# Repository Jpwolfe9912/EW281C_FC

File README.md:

# EW281C_FC
Flight Controller for EW281C

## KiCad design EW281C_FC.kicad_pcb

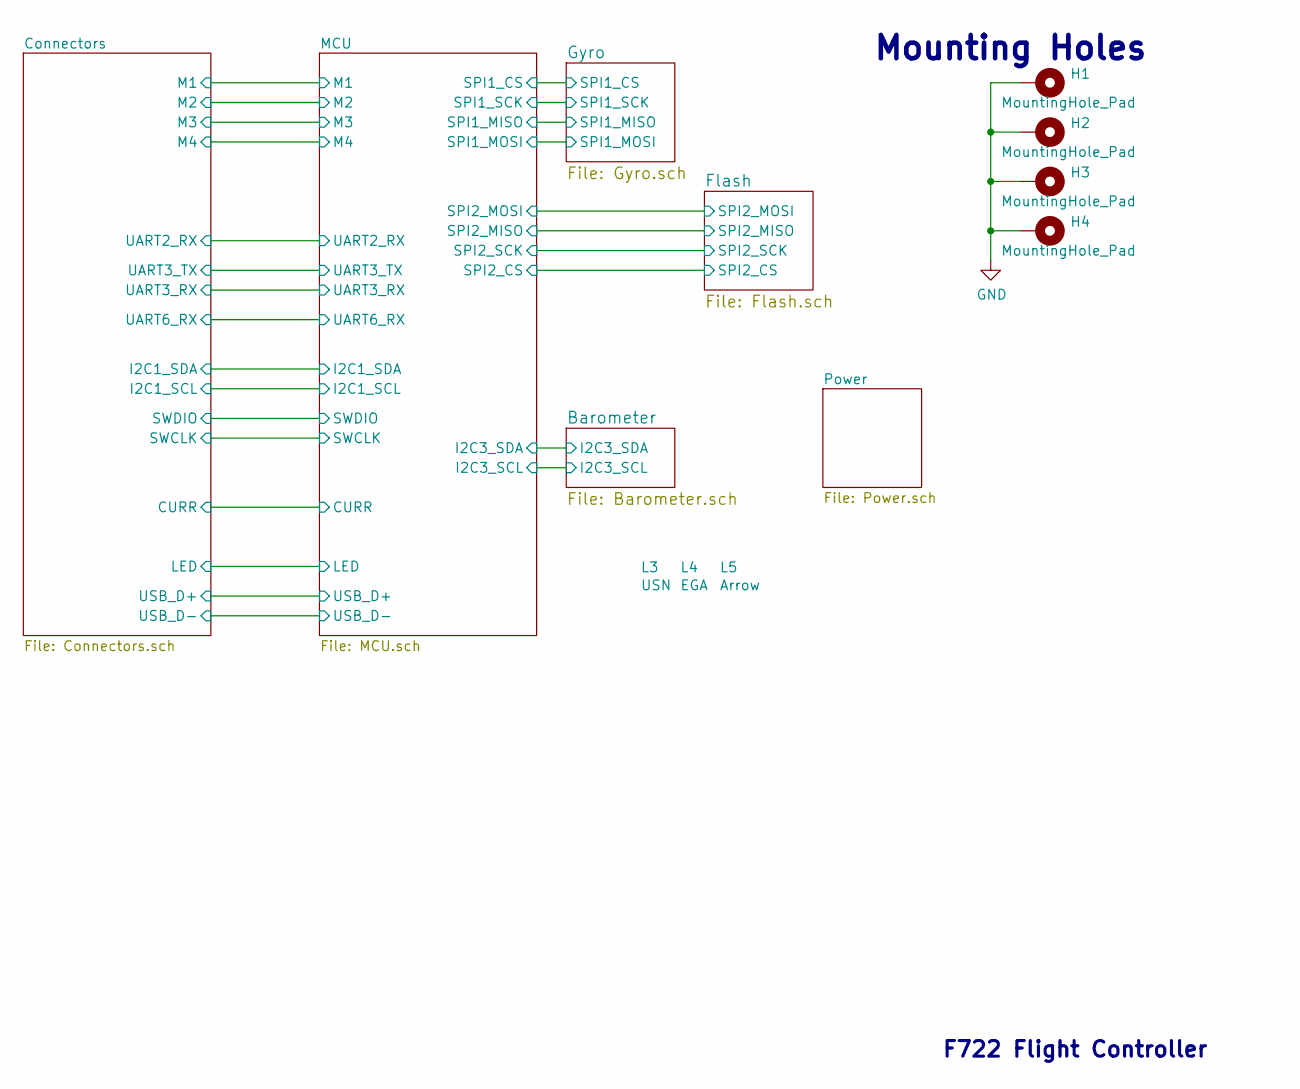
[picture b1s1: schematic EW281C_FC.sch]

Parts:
H1, H2, H3, H4: MountingHole_Pad; MountingHole_3mm_M2_20x20
L3: USN
L4: EGA
L5: Arrow

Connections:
GND: H1.1, H2.1, H3.1, H4.1; also elsewhere on the board

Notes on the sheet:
Mounting Holes
F722 Flight Controller

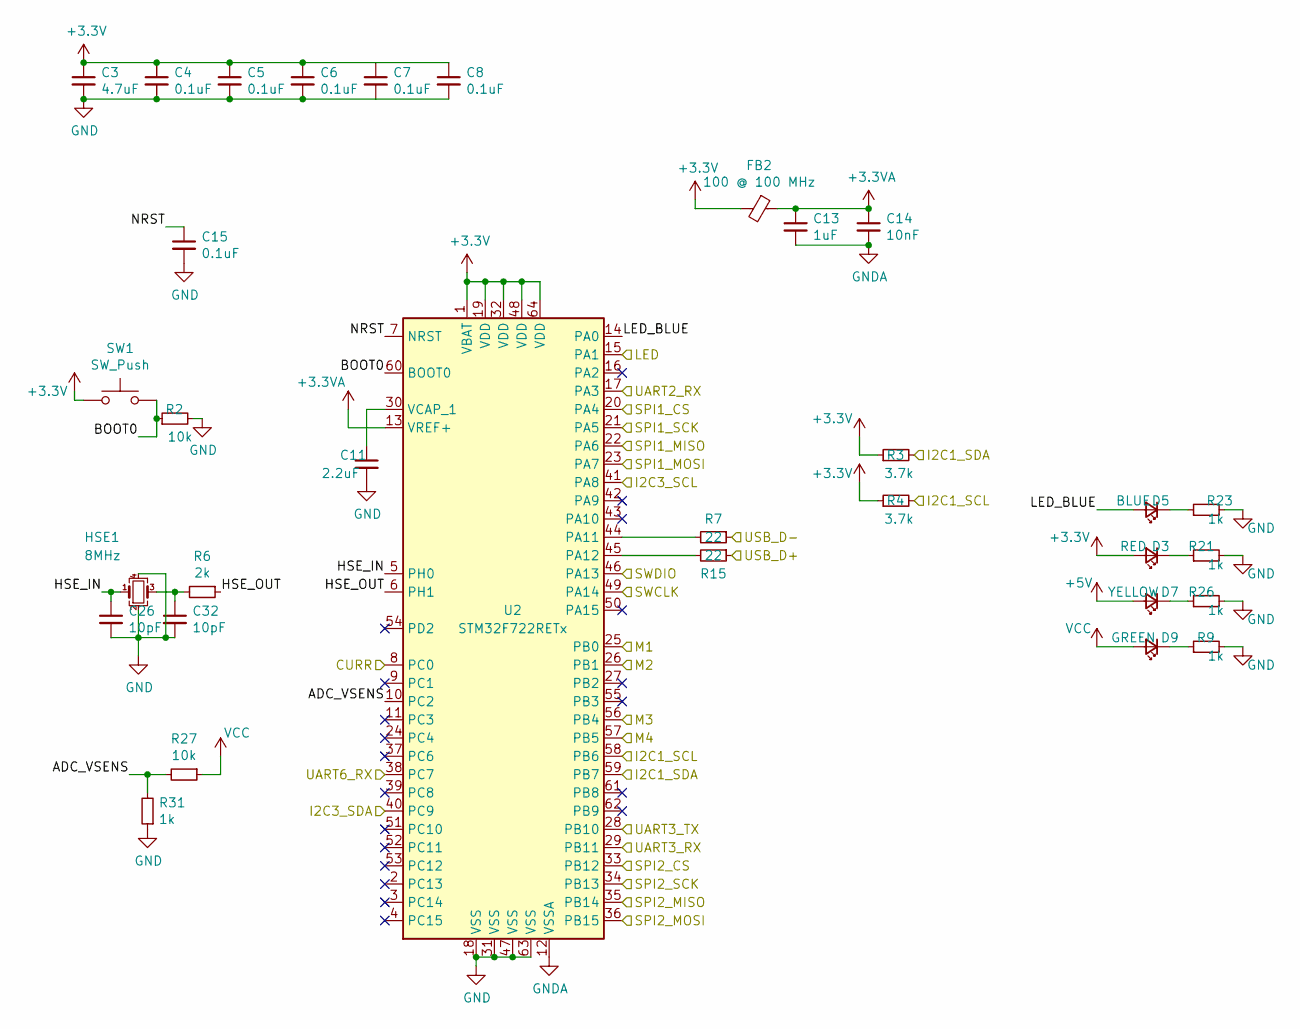
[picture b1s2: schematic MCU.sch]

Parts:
C3: 4.7uF; C_0402_1005Metric
C4, C5, C6, C7, C8, C15: 0.1uF; C_0402_1005Metric
C11: 2.2uF; C_0402_1005Metric
C13: 1uF; C_0402_1005Metric
C14: 10nF; C_0402_1005Metric
C26, C32: 10pF; C_0402_1005Metric
D3: RED; LED_0603_1608Metric
D5: BLUE; LED_0603_1608Metric
D7: YELLOW; LED_0603_1608Metric
D9: GREEN; LED_0603_1608Metric
FB2: 100 @ 100 MHz; L_0603_1608Metric
HSE1: 8MHz; Oscillator_SMD_Abracon_ASE-4Pin_3.2x2.5mm
R2, R27: 10k; R_0402_1005Metric
R3, R4: 3.7k; R_0402_1005Metric
R6: 2k; R_0402_1005Metric
R7, R15: 22; R_0402_1005Metric
R9, R21, R23, R26, R31: 1k; R_0402_1005Metric
SW1: SW_Push; SW_SPST_B3U-1000P
U2: STM32F722RETx; LQFP-64_10x10mm_P0.5mm

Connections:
+3.3VA: C13.1, C14.1, FB2.1, U2.13 (VREF+)
+5V: D7.2 (A); also elsewhere on the board
/Barometer/I2C3_SCL: U2.41 (PA8); also elsewhere on the board
/Barometer/I2C3_SDA: U2.40 (PC9); also elsewhere on the board
/Connectors/CURR: U2.8 (PC0); also elsewhere on the board
/Connectors/I2C1_SCL: R4.2, U2.58 (PB6); also elsewhere on the board
/Connectors/I2C1_SDA: R3.2, U2.59 (PB7); also elsewhere on the board
/Connectors/LED: U2.15 (PA1); also elsewhere on the board
/Connectors/M1: U2.25 (PB0); also elsewhere on the board
/Connectors/M2: U2.26 (PB1); also elsewhere on the board
/Connectors/M3: U2.56 (PB4); also elsewhere on the board
/Connectors/M4: U2.57 (PB5); also elsewhere on the board
/Connectors/SWCLK: U2.49 (PA14); also elsewhere on the board
/Connectors/SWDIO: U2.46 (PA13); also elsewhere on the board
/Connectors/UART2_RX: U2.17 (PA3); also elsewhere on the board
/Connectors/UART3_RX: U2.29 (PB11); also elsewhere on the board
/Connectors/UART3_TX: U2.28 (PB10); also elsewhere on the board
/Connectors/UART6_RX: U2.38 (PC7); also elsewhere on the board
/Connectors/USB_D+: R15.1; also elsewhere on the board
/Connectors/USB_D-: R7.1; also elsewhere on the board
/Flash/SPI2_CS: U2.33 (PB12); also elsewhere on the board
/Flash/SPI2_MISO: U2.35 (PB14); also elsewhere on the board
/Flash/SPI2_MOSI: U2.36 (PB15); also elsewhere on the board
/Flash/SPI2_SCK: U2.34 (PB13); also elsewhere on the board
/Gyro/SPI1_CS: U2.20 (PA4); also elsewhere on the board
/Gyro/SPI1_MISO: U2.22 (PA6); also elsewhere on the board
/Gyro/SPI1_MOSI: U2.23 (PA7); also elsewhere on the board
/Gyro/SPI1_SCK: U2.21 (PA5); also elsewhere on the board
/MCU/ADC_VSENS: R27.2, R31.2, U2.10 (PC2)
/MCU/BOOT0: R2.1, SW1.2, U2.60 (BOOT0)
/MCU/HSE_IN: C26.1, HSE1.1, U2.5 (PH0)
/MCU/HSE_OUT: R6.1, U2.6 (PH1)
/MCU/LED_BLUE: D5.2 (A), U2.14 (PA0)
/MCU/NRST: C15.1, U2.7 (NRST)
GND: C3.2, C4.2, C5.2, C6.2, C7.2, C8.2, C11.2, C15.2, C26.2, C32.2, HSE1.2, HSE1.4, R2.2, R9.2, R21.2, R23.2, R26.2, R31.1, U2.18 (VSS), U2.31 (VSS), U2.47 (VSS), U2.63 (VSS); also elsewhere on the board
GNDA: C13.2, C14.2, U2.12 (VSSA)
unnamed: C11.1, U2.30 (VCAP_1)
unnamed: C32.1, HSE1.3, R6.2
unnamed: D3.1 (K), R21.1
unnamed: D5.1 (K), R23.1
unnamed: D7.1 (K), R26.1
unnamed: D9.1 (K), R9.1
unnamed: R7.2, U2.44 (PA11)
unnamed: R15.2, U2.45 (PA12)
VCC: D9.2 (A), R27.1; also elsewhere on the board

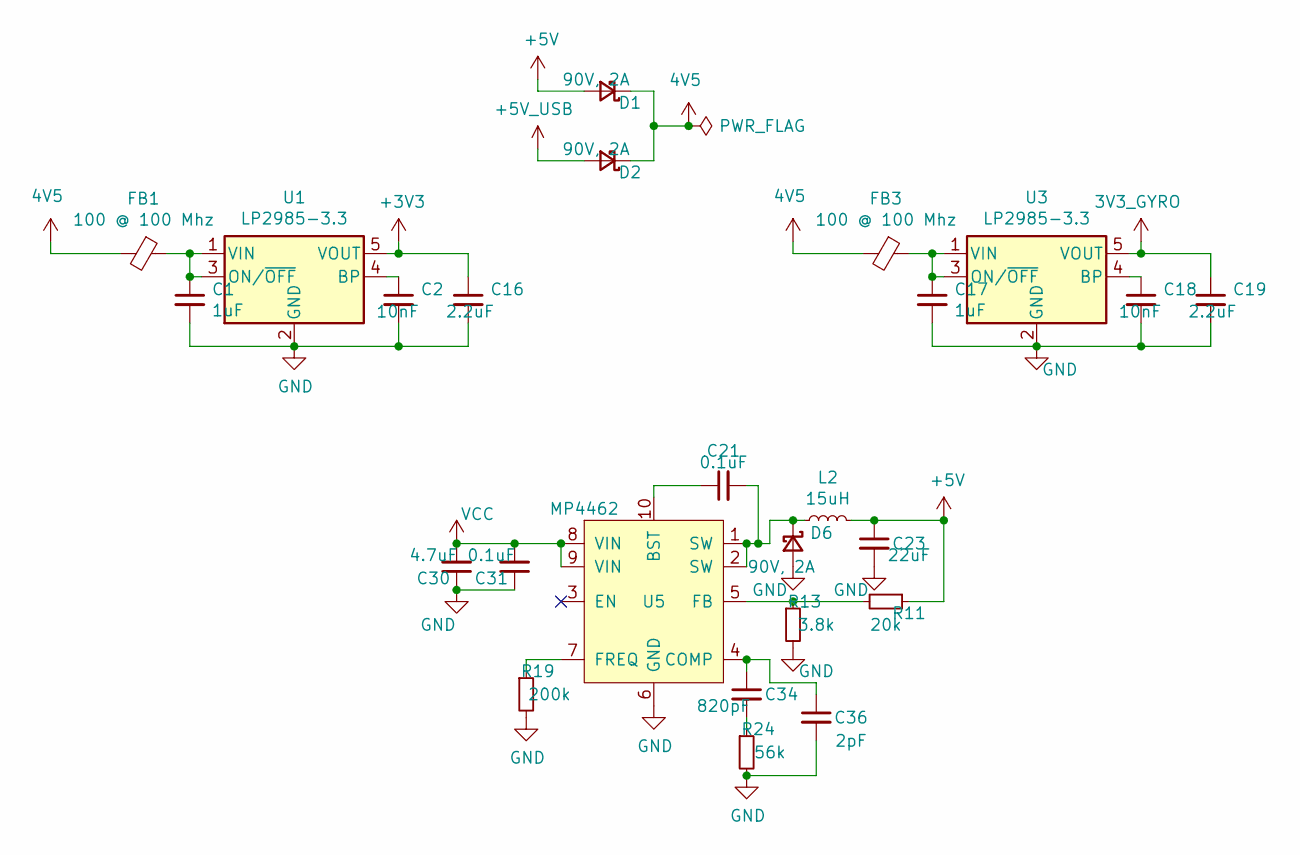
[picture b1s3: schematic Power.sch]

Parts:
C1, C17: 1uF; C_0402_1005Metric
C2, C18: 10nF; C_0402_1005Metric
C16, C19: 2.2uF; C_0402_1005Metric
C21, C31: 0.1uF; C_0402_1005Metric
C23: 22uF; C_0603_1608Metric
C30: 4.7uF; C_0603_1608Metric
C34: 820pF; C_0402_1005Metric
C36: 2pF; C_0402_1005Metric
D1, D2, D6: 90V, 2A; D_SOD-123F
FB1, FB3: 100 @ 100 Mhz; L_0603_1608Metric
L2: 15uH; L_Bourns-SRN3015
R11: 20k; R_0402_1005Metric
R13: 3.8k; R_0402_1005Metric
R19: 200k; R_0402_1005Metric
R24: 56k; R_0402_1005Metric
U1, U3: LP2985-3.3; SOT-23-5
U5: MP4462; DFN-10-1EP_3x3mm_P0.5mm_EP1.7x2.5mm

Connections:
4V5: D1.1 (K), D2.1 (K), FB1.2, FB3.2
+3V3_GYRO: C19.1, U3.5 (VOUT); also elsewhere on the board
+5V: C23.1, D1.2 (A), L2.2, R11.1; also elsewhere on the board
+5V_USB: D2.2 (A); also elsewhere on the board
GND: C1.2, C2.2, C16.2, C17.2, C18.2, C19.2, C23.2, C30.1, C31.1, C36.2, D6.2 (A), R13.2, R19.2, R24.2, U1.2 (GND), U3.2 (GND), U5.6 (GND); also elsewhere on the board
unnamed: C1.1, FB1.1, U1.1 (VIN), U1.3 (ON/~OFF~)
unnamed: C2.1, U1.4 (BP)
unnamed: C17.1, FB3.1, U3.1 (VIN), U3.3 (ON/~OFF~)
unnamed: C18.1, U3.4 (BP)
unnamed: C21.1, U5.10 (BST)
unnamed: C21.2, D6.1 (K), L2.1, U5.1 (SW), U5.2 (SW)
unnamed: C34.1, C36.1, U5.4 (COMP)
unnamed: C34.2, R24.1
unnamed: R11.2, R13.1, U5.5 (FB)
unnamed: R19.1, U5.7 (FREQ)
VCC: C30.2, C31.2, U5.8 (VIN), U5.9 (VIN); also elsewhere on the board

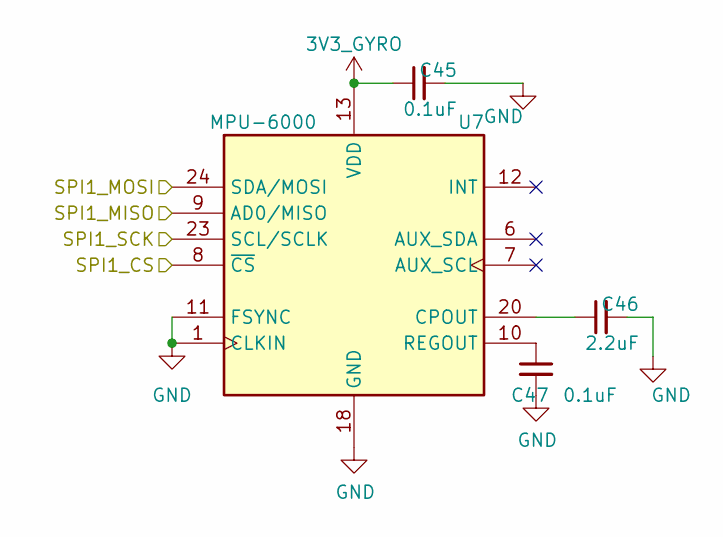
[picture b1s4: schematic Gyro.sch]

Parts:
C45, C47: 0.1uF; C_0402_1005Metric
C46: 2.2uF; C_0402_1005Metric
U7: MPU-6000; InvenSense_QFN-24_4x4mm_P0.5mm

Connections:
+3V3_GYRO: C45.1, U7.13 (VDD); also elsewhere on the board
/Gyro/SPI1_CS: U7.8 (~CS); also elsewhere on the board
/Gyro/SPI1_MISO: U7.9 (AD0/MISO); also elsewhere on the board
/Gyro/SPI1_MOSI: U7.24 (SDA/MOSI); also elsewhere on the board
/Gyro/SPI1_SCK: U7.23 (SCL/SCLK); also elsewhere on the board
GND: C45.2, C46.2, C47.2, U7.1 (CLKIN), U7.11 (FSYNC), U7.18 (GND); also elsewhere on the board
unnamed: C46.1, U7.20 (CPOUT)
unnamed: C47.1, U7.10 (REGOUT)

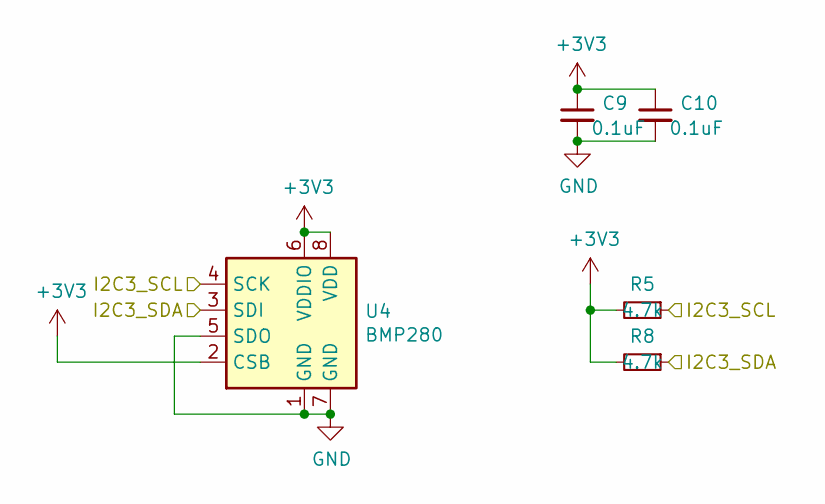
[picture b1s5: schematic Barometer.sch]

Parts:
C9, C10: 0.1uF; C_0402_1005Metric
R5, R8: 4.7k; R_0402_1005Metric
U4: BMP280; Bosch_LGA-8_2x2.5mm_P0.65mm_ClockwisePinNumbering

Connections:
/Barometer/I2C3_SCL: R5.1, U4.4 (SCK); also elsewhere on the board
/Barometer/I2C3_SDA: R8.1, U4.3 (SDI); also elsewhere on the board
GND: C9.2, C10.2, U4.1 (GND), U4.5 (SDO), U4.7 (GND); also elsewhere on the board

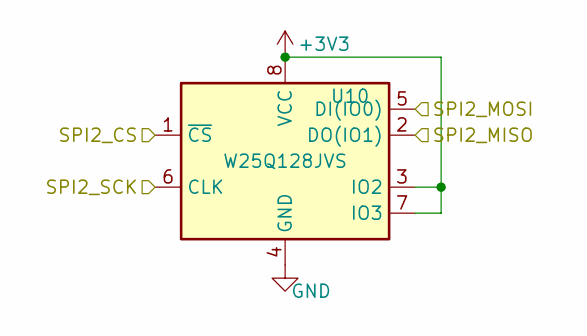
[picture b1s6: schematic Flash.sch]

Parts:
U10: W25Q128JVS; SOIC-8_5.23x5.23mm_P1.27mm

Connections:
/Flash/SPI2_CS: U10.1 (~CS); also elsewhere on the board
/Flash/SPI2_MISO: U10.2 (DO(IO1)); also elsewhere on the board
/Flash/SPI2_MOSI: U10.5 (DI(IO0)); also elsewhere on the board
/Flash/SPI2_SCK: U10.6 (CLK); also elsewhere on the board
GND: U10.4 (GND); also elsewhere on the board

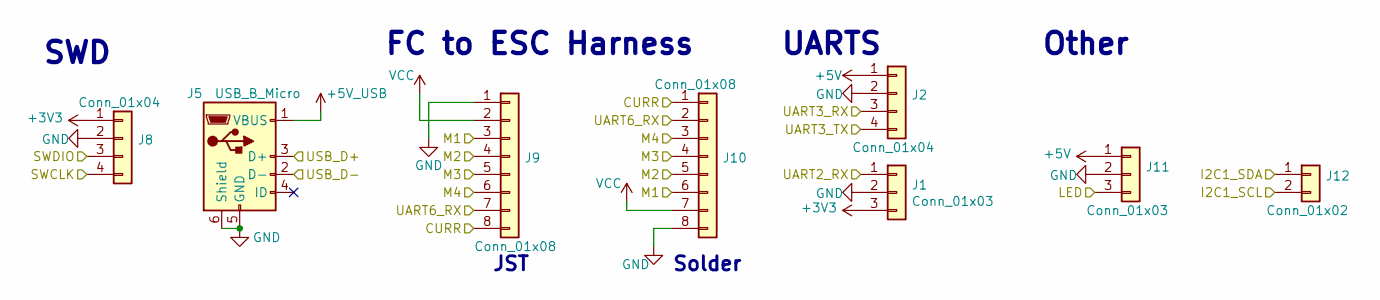
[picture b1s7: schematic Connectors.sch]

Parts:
J1, J11: Conn_01x03; JST_SH_SM03B-SRSS-TB_1x03-1MP_P1.00mm_Horizontal
J2: Conn_01x04; Conn_4Pin
J5: USB_B_Micro; USB_Micro-B_GCT_USB3076-30-A
J8: Conn_01x04; PinHeader_1x04_P2.54mm_Vertical
J9: Conn_01x08; JST_SH_SM08B-SRSS-TB_1x08-1MP_P1.00mm_Horizontal
J10: Conn_01x08; Conn_FC_Solder_8
J12: Conn_01x02; Conn_2Pin

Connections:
+5V: J2.1, J11.1; also elsewhere on the board
+5V_USB: J5.1 (VBUS); also elsewhere on the board
/Connectors/CURR: J9.8, J10.1; also elsewhere on the board
/Connectors/I2C1_SCL: J12.2; also elsewhere on the board
/Connectors/I2C1_SDA: J12.1; also elsewhere on the board
/Connectors/LED: J11.3; also elsewhere on the board
/Connectors/M1: J9.3, J10.6; also elsewhere on the board
/Connectors/M2: J9.4, J10.5; also elsewhere on the board
/Connectors/M3: J9.5, J10.4; also elsewhere on the board
/Connectors/M4: J9.6, J10.3; also elsewhere on the board
/Connectors/SWCLK: J8.4; also elsewhere on the board
/Connectors/SWDIO: J8.3; also elsewhere on the board
/Connectors/UART2_RX: J1.1; also elsewhere on the board
/Connectors/UART3_RX: J2.3; also elsewhere on the board
/Connectors/UART3_TX: J2.4; also elsewhere on the board
/Connectors/UART6_RX: J9.7, J10.2; also elsewhere on the board
/Connectors/USB_D+: J5.3 (D+); also elsewhere on the board
/Connectors/USB_D-: J5.2 (D-); also elsewhere on the board
GND: J1.2, J2.2, J5.5 (GND), J5.6 (Shield), J8.2, J9.1, J10.8, J11.2; also elsewhere on the board
VCC: J9.2, J10.7; also elsewhere on the board

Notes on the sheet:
FC to ESC Harness
UARTS
SWD
Other
JST
Solder

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
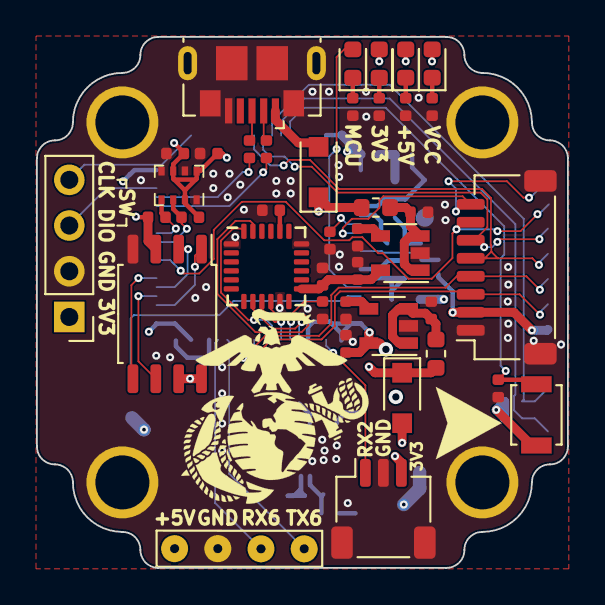
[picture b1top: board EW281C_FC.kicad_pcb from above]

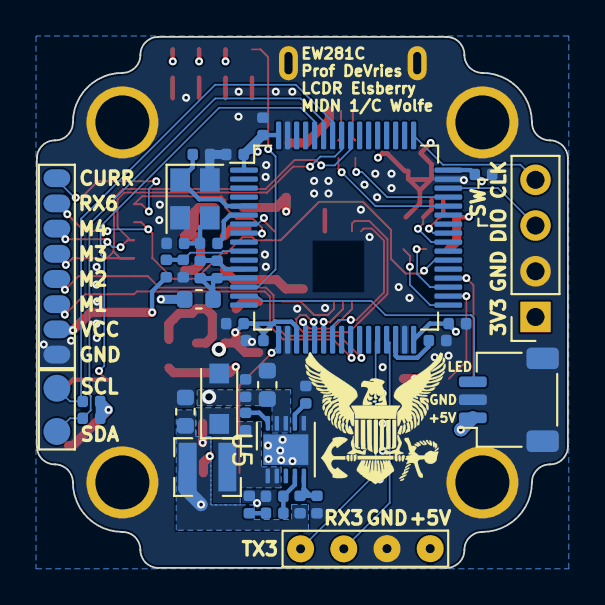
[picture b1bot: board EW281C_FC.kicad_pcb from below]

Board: 4 copper layers, 29.5 x 29.5 mm, 82 parts (36 on the bottom side), 61 nets.

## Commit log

2021-04-29 Finished laying out and routing. Still under review
2021-04-29 Small cleanups
2021-05-18 Added trace for 3V3
2021-05-18 Added LED for VCC
2021-05-18 Moved GND symbol slightly
2021-05-18 Added PNGs
2021-05-18 Added 3D PNGs
2021-05-18 Added logos
2021-06-17 Changed to 20x20 form factor
2021-06-27 Changes made
2021-06-28 Changed some components to match what is in stock
